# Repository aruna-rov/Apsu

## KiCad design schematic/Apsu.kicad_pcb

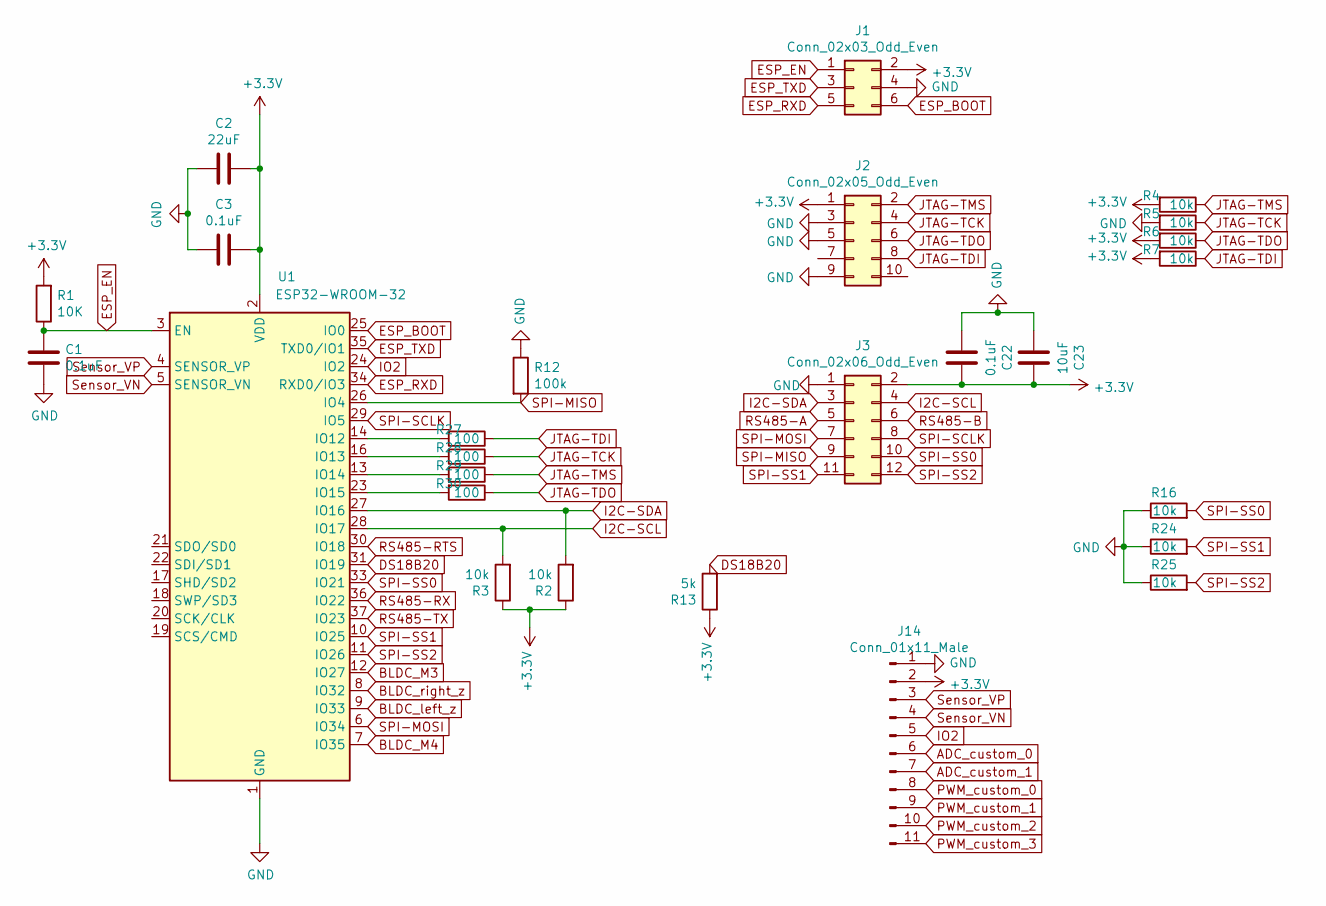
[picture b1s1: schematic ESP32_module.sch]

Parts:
C1, C3, C22: 0.1uF; C_0805_2012Metric_Pad1.15x1.40mm_HandSolder; MPN C0805C104J5RACTU
C2: 22uF; C_0805_2012Metric_Pad1.15x1.40mm_HandSolder; MPN C0805C226K9PACTU
C23: 10uF; C_0805_2012Metric_Pad1.15x1.40mm_HandSolder; MPN C0805C106K8PACTU
J1: Conn_02x03_Odd_Even; PinHeader_2x03_P1.27mm_Vertical_IDC; MPN GRPB032VWVN-RC
J2: Conn_02x05_Odd_Even; 10pin1.27mmIDC; MPN 3220-10-0100-00
J3: Conn_02x06_Odd_Even; IDC-Header_2x06_P2.54mm_Vertical; MPN BHR-12-VUA
J14: Conn_01x11_Male; PinHeader_1x11_P2.54mm_Vertical
R1: 10K; R_0805_2012Metric_Pad1.15x1.40mm_HandSolder; MPN ERA-6AEB103V
R2, R3, R4, R5, R6, R7, R16, R24, R25: 10k; R_0805_2012Metric_Pad1.15x1.40mm_HandSolder; MPN ERA-6AEB103V
R12: 100k; R_0805_2012Metric_Pad1.15x1.40mm_HandSolder; MPN ERA-6AEB104V
R13: 5k; R_0805_2012Metric_Pad1.15x1.40mm_HandSolder; MPN ERA6AEB4991V
R27, R28, R29, R30: 100; R_0805_2012Metric_Pad1.15x1.40mm_HandSolder; MPN ERA6AEB101V
U1: ESP32-WROOM-32; MPN ESP32-WROOM-32D

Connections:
+3V3: C2.2, C3.2, C22.2, C23.2, J1.2, J2.1, J3.2, J14.2, R1.2, R2.1, R3.1, R4.2, R6.2, R7.2, R13.1, U1.2 (VDD); also elsewhere on the board
ADC_custom_0: J14.6; also elsewhere on the board
ADC_custom_1: J14.7; also elsewhere on the board
BLDC_M3: U1.12 (IO27); also elsewhere on the board
BLDC_M4: U1.7 (IO35); also elsewhere on the board
BLDC_left_z: U1.9 (IO33); also elsewhere on the board
BLDC_right_z: U1.8 (IO32); also elsewhere on the board
DS18B20: R13.2, U1.31 (IO19); also elsewhere on the board
ESP_BOOT: J1.6, U1.25 (IO0)
ESP_EN: C1.1, J1.1, R1.1, U1.3 (EN)
ESP_RXD: J1.5, U1.34 (RXD0/IO3)
ESP_TXD: J1.3, U1.35 (TXD0/IO1)
GND: C1.2, C2.1, C3.1, C22.1, C23.1, J1.4, J2.3, J2.5, J2.9, J3.1, J14.1, R5.2, R12.1, R16.1, R24.1, R25.1, U1.1 (GND), U1.15 (GND), U1.38 (GND), U1.39 (GND); also elsewhere on the board
I2C-SCL: J3.4, R3.2, U1.28 (IO17); also elsewhere on the board
I2C-SDA: J3.3, R2.2, U1.27 (IO16); also elsewhere on the board
IO2: J14.5, U1.24 (IO2)
JTAG-TCK: J2.4, R5.1, R28.1
JTAG-TDI: J2.8, R7.1, R27.1
JTAG-TDO: J2.6, R6.1, R30.1
JTAG-TMS: J2.2, R4.1, R29.1
unnamed: R27.2, U1.14 (IO12)
unnamed: R28.2, U1.16 (IO13)
unnamed: R29.2, U1.13 (IO14)
unnamed: R30.2, U1.23 (IO15)
PWM_custom_0: J14.8; also elsewhere on the board
PWM_custom_1: J14.9; also elsewhere on the board
PWM_custom_2: J14.10; also elsewhere on the board
PWM_custom_3: J14.11; also elsewhere on the board
RS485-A: J3.5; also elsewhere on the board
RS485-B: J3.6; also elsewhere on the board
RS485-RTS: U1.30 (IO18); also elsewhere on the board
RS485-RX: U1.36 (IO22); also elsewhere on the board
RS485-TX: U1.37 (IO23); also elsewhere on the board
SPI-MISO: J3.9, R12.2, U1.26 (IO4); also elsewhere on the board
SPI-MOSI: J3.7, U1.6 (IO34)
SPI-SCLK: J3.8, U1.29 (IO5); also elsewhere on the board
SPI-SS0: J3.10, R16.2, U1.33 (IO21); also elsewhere on the board
SPI-SS1: J3.11, R24.2, U1.10 (IO25); also elsewhere on the board
SPI-SS2: J3.12, R25.2, U1.11 (IO26); also elsewhere on the board
Sensor_VN: J14.4, U1.5 (SENSOR_VN)
Sensor_VP: J14.3, U1.4 (SENSOR_VP)

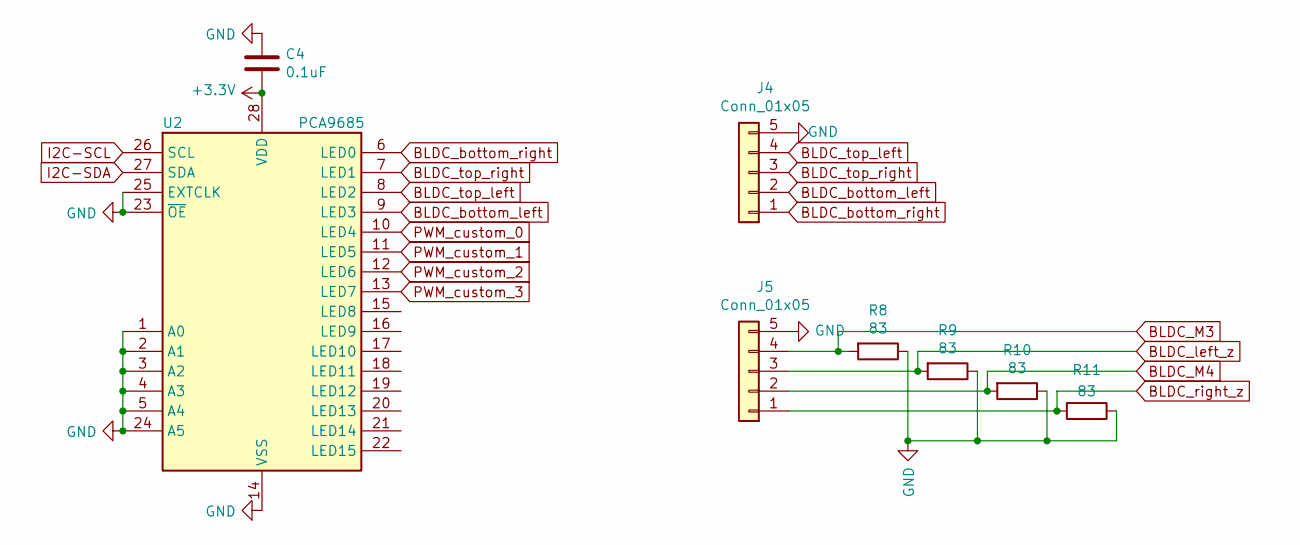
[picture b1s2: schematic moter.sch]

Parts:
C4: 0.1uF; C_0805_2012Metric_Pad1.15x1.40mm_HandSolder; MPN C0805C104J5RACTU
J4, J5: Conn_01x05; JST_XH_B5B-XH-A_1x05_P2.50mm_Vertical; MPN B5B-XH-A(LF)(SN)
R8, R9, R10, R11: 83; R_0805_2012Metric_Pad1.15x1.40mm_HandSolder; MPN ERA-6AEB820V
U2: PCA9685; NXP_Semiconductors-SOT788-1-02_2016-0-MFG; MPN PCA9685BS,118

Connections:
+3V3: C4.2, U2.28 (VDD); also elsewhere on the board
BLDC_M3: J5.4, R8.2; also elsewhere on the board
BLDC_M4: J5.2, R10.2; also elsewhere on the board
BLDC_bottom_left: J4.2, U2.9 (LED3)
BLDC_bottom_right: J4.1, U2.6 (LED0)
BLDC_left_z: J5.3, R9.2; also elsewhere on the board
BLDC_right_z: J5.1, R11.2; also elsewhere on the board
BLDC_top_left: J4.4, U2.8 (LED2)
BLDC_top_right: J4.3, U2.7 (LED1)
GND: C4.1, J4.5, J5.5, R8.1, R9.1, R10.1, R11.1, U2.1 (A0), U2.2 (A1), U2.3 (A2), U2.4 (A3), U2.5 (A4), U2.14 (VSS), U2.23 (~OE), U2.24 (A5), U2.25 (EXTCLK); also elsewhere on the board
I2C-SCL: U2.26 (SCL); also elsewhere on the board
I2C-SDA: U2.27 (SDA); also elsewhere on the board
PWM_custom_0: U2.10 (LED4); also elsewhere on the board
PWM_custom_1: U2.11 (LED5); also elsewhere on the board
PWM_custom_2: U2.12 (LED6); also elsewhere on the board
PWM_custom_3: U2.13 (LED7); also elsewhere on the board

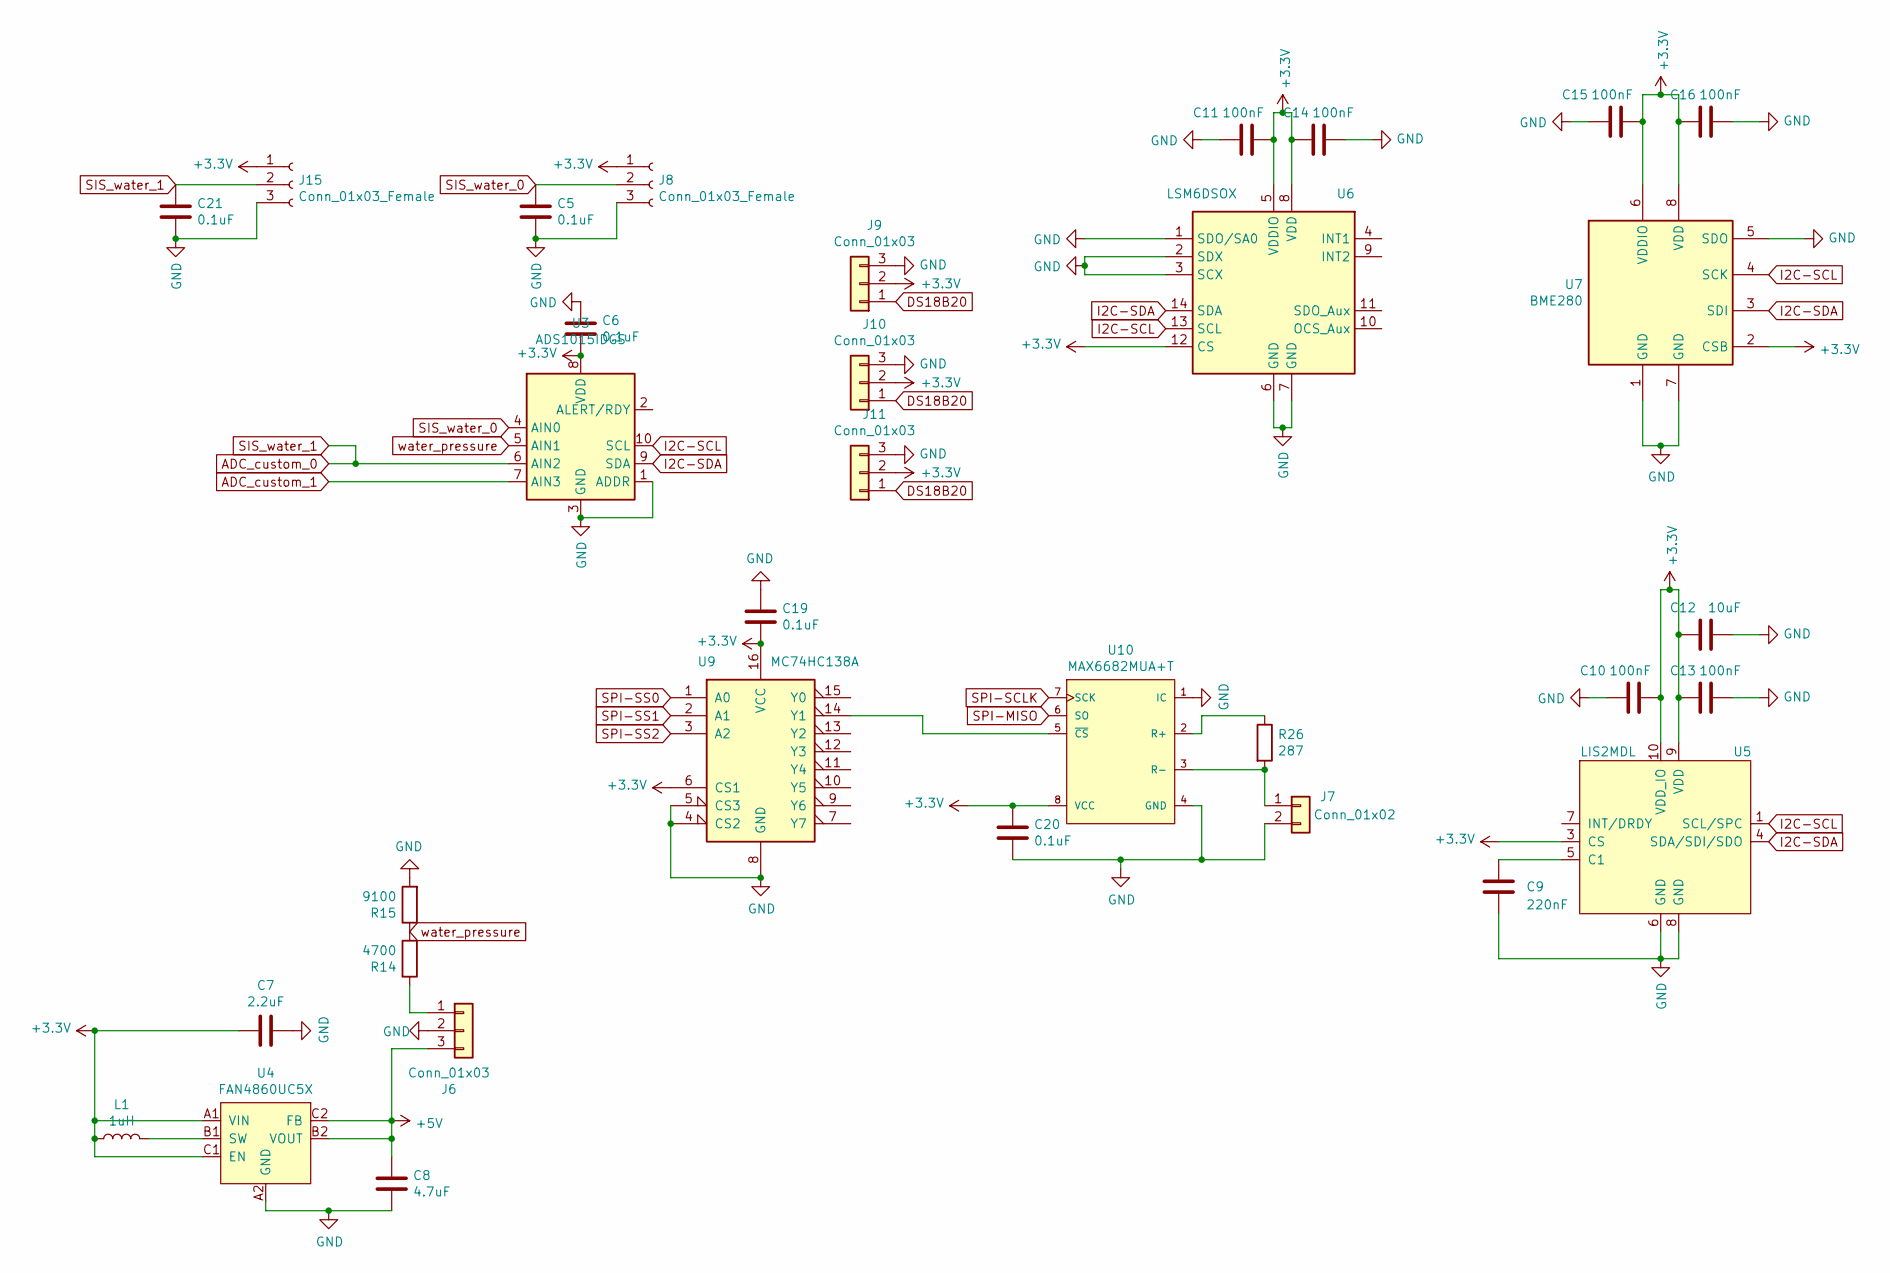
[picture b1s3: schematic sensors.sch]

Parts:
C5, C6, C19, C20, C21: 0.1uF; C_0805_2012Metric_Pad1.15x1.40mm_HandSolder; MPN C0805C104J5RACTU
C7: 2.2uF; C_0805_2012Metric_Pad1.15x1.40mm_HandSolder; MPN C0805C225K4RACTU
C8: 4.7uF; C_0805_2012Metric_Pad1.15x1.40mm_HandSolder; MPN C0805C475K3PACTU
C9: 220nF; C_0805_2012Metric_Pad1.15x1.40mm_HandSolder; MPN C0805C224K5RACTU
C10, C11, C13, C14, C15, C16: 100nF; C_0805_2012Metric_Pad1.15x1.40mm_HandSolder; MPN C0805C104J5RACTU
C12: 10uF; C_0805_2012Metric_Pad1.15x1.40mm_HandSolder; MPN C0805C106K8PACTU
J6, J9, J10, J11: Conn_01x03; JST_XH_B3B-XH-A_1x03_P2.50mm_Vertical; MPN B3B-XH-A(LF)(SN)
J7: Conn_01x02; JST_XH_B2B-XH-A_1x02_P2.50mm_Vertical; MPN B2B-XH-A(LF)(SN)
J8, J15: Conn_01x03_Female; JST_XH_B3B-XH-A_1x03_P2.50mm_Vertical; MPN B3B-XH-A(LF)(SN)
L1: 1uH; L_0805_2012Metric_Pad1.15x1.40mm_HandSolder; MPN LQM21NN1R0K10D
R14: 4700; R_0805_2012Metric_Pad1.15x1.40mm_HandSolder; MPN ERA-6AEB472V
R15: 9100; R_0805_2012Metric_Pad1.15x1.40mm_HandSolder; MPN ERA6AEB912V
R26: 287; R_0805_2012Metric_Pad1.15x1.40mm_HandSolder; MPN ERA-6AEB301V
U3: ADS1015IDGS; TSSOP-10_3x3mm_P0.5mm; MPN ADS1015IDGS
U4: FAN4860UC5X; WLCSP-6_1.4x1.0mm_P0.4mm; MPN FAN4860UC5X
U5: LIS2MDL; LGA-12_2x2mm_P0.5mm; MPN LIS2MDLTR
U6: LSM6DSOX; LGA-14_3x2.5mm_P0.5mm_LayoutBorder3x4y; MPN LSM6DSOXTR
U7: BME280; Bosch_LGA-8_2.5x2.5mm_P0.65mm_ClockwisePinNumbering; MPN BME280
U9: MC74HC138A; TSSOP-16_4.4x5mm_P0.65mm; MPN MC74HC138ADTR2G
U10: MAX6682MUA+T; Maxim-MAX6682MUA+T-Level_A; MPN MAX6682MUA+T

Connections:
+3V3: C6.2, C7.2, C10.2, C11.2, C12.1, C13.1, C14.1, C15.2, C16.1, C19.2, C20.1, J8.1, J9.2, J10.2, J11.2, J15.1, L1.1, U3.8 (VDD), U4.A1 (VIN), U4.C1 (EN), U5.3 (CS), U5.9 (VDD), U5.10 (VDD_IO), U6.5 (VDDIO), U6.8 (VDD), U6.12 (CS), U7.2 (CSB), U7.6 (VDDIO), U7.8 (VDD), U9.6 (CS1), U9.16 (VCC), U10.8 (VCC); also elsewhere on the board
+5V: C8.1, J6.3, U4.B2 (VOUT), U4.C2 (FB)
ADC_custom_0: C21.1, J15.2, U3.6 (AIN2); also elsewhere on the board
ADC_custom_1: U3.7 (AIN3); also elsewhere on the board
DS18B20: J9.1, J10.1, J11.1; also elsewhere on the board
GND: C5.2, C6.1, C7.1, C8.2, C9.2, C10.1, C11.1, C12.2, C13.2, C14.2, C15.1, C16.2, C19.1, C20.2, C21.2, J6.2, J7.2, J8.3, J9.3, J10.3, J11.3, J15.3, R15.2, U3.1 (ADDR), U3.3 (GND), U4.A2 (GND), U5.6 (GND), U5.8 (GND), U6.1 (SDO/SA0), U6.2 (SDX), U6.3 (SCX), U6.6 (GND), U6.7 (GND), U7.1 (GND), U7.5 (SDO), U7.7 (GND), U9.4 (CS2), U9.5 (CS3), U9.8 (GND), U10.1 (IC), U10.4 (GND); also elsewhere on the board
I2C-SCL: U3.10 (SCL), U5.1 (SCL/SPC), U6.13 (SCL), U7.4 (SCK); also elsewhere on the board
I2C-SDA: U3.9 (SDA), U5.4 (SDA/SDI/SDO), U6.14 (SDA), U7.3 (SDI); also elsewhere on the board
unnamed: C9.1, U5.5 (C1)
unnamed: J6.1, R14.1
unnamed: J7.1, R26.2, U10.3 (R-)
unnamed: L1.2, U4.B1 (SW)
unnamed: R26.1, U10.2 (R+)
unnamed: U9.14 (Y1), U10.5 (~CS~)
SIS_water_0: C5.1, J8.2, U3.4 (AIN0)
SPI-MISO: U10.6 (SO); also elsewhere on the board
SPI-SCLK: U10.7 (SCK); also elsewhere on the board
SPI-SS0: U9.1 (A0); also elsewhere on the board
SPI-SS1: U9.2 (A1); also elsewhere on the board
SPI-SS2: U9.3 (A2); also elsewhere on the board
water_pressure: R14.2, R15.1, U3.5 (AIN1)

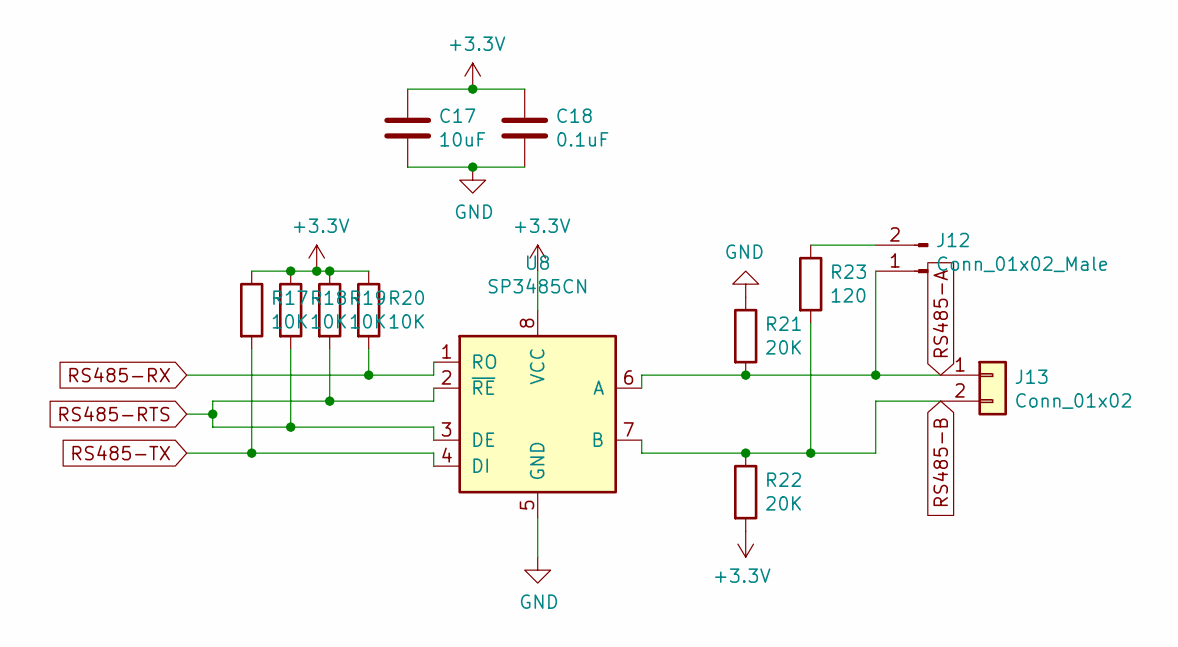
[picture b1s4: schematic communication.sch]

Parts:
C17: 10uF; C_0805_2012Metric_Pad1.15x1.40mm_HandSolder; MPN C0805C106K8PACTU
C18: 0.1uF; C_0805_2012Metric_Pad1.15x1.40mm_HandSolder; MPN C0805C104J5RACTU
J12: Conn_01x02_Male; PinHeader_1x02_P2.54mm_Vertical
J13: Conn_01x02; JST_XH_B2B-XH-A_1x02_P2.50mm_Vertical; MPN B2B-XH-A(LF)(SN)
R17, R18, R19, R20: 10K; R_0805_2012Metric_Pad1.15x1.40mm_HandSolder; MPN ERA-6AEB103V
R21, R22: 20K; R_0805_2012Metric_Pad1.15x1.40mm_HandSolder; MPN ERA6AEB203V
R23: 120; R_0805_2012Metric_Pad1.15x1.40mm_HandSolder; MPN ERJ-6ENF1200V
U8: SP3485CN; SOIC-8_3.9x4.9mm_P1.27mm; MPN MAX485CSA+

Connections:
+3V3: C17.1, C18.1, R17.1, R18.1, R19.1, R20.1, R22.2, U8.8 (VCC); also elsewhere on the board
GND: C17.2, C18.2, R21.1, U8.5 (GND); also elsewhere on the board
unnamed: J12.2, R23.1
RS485-A: J12.1, J13.1, R21.2, U8.6 (A); also elsewhere on the board
RS485-B: J13.2, R22.1, R23.2, U8.7 (B); also elsewhere on the board
RS485-RTS: R18.2, R19.2, U8.2 (~RE~), U8.3 (DE); also elsewhere on the board
RS485-RX: R20.2, U8.1 (RO); also elsewhere on the board
RS485-TX: R17.2, U8.4 (DI); also elsewhere on the board

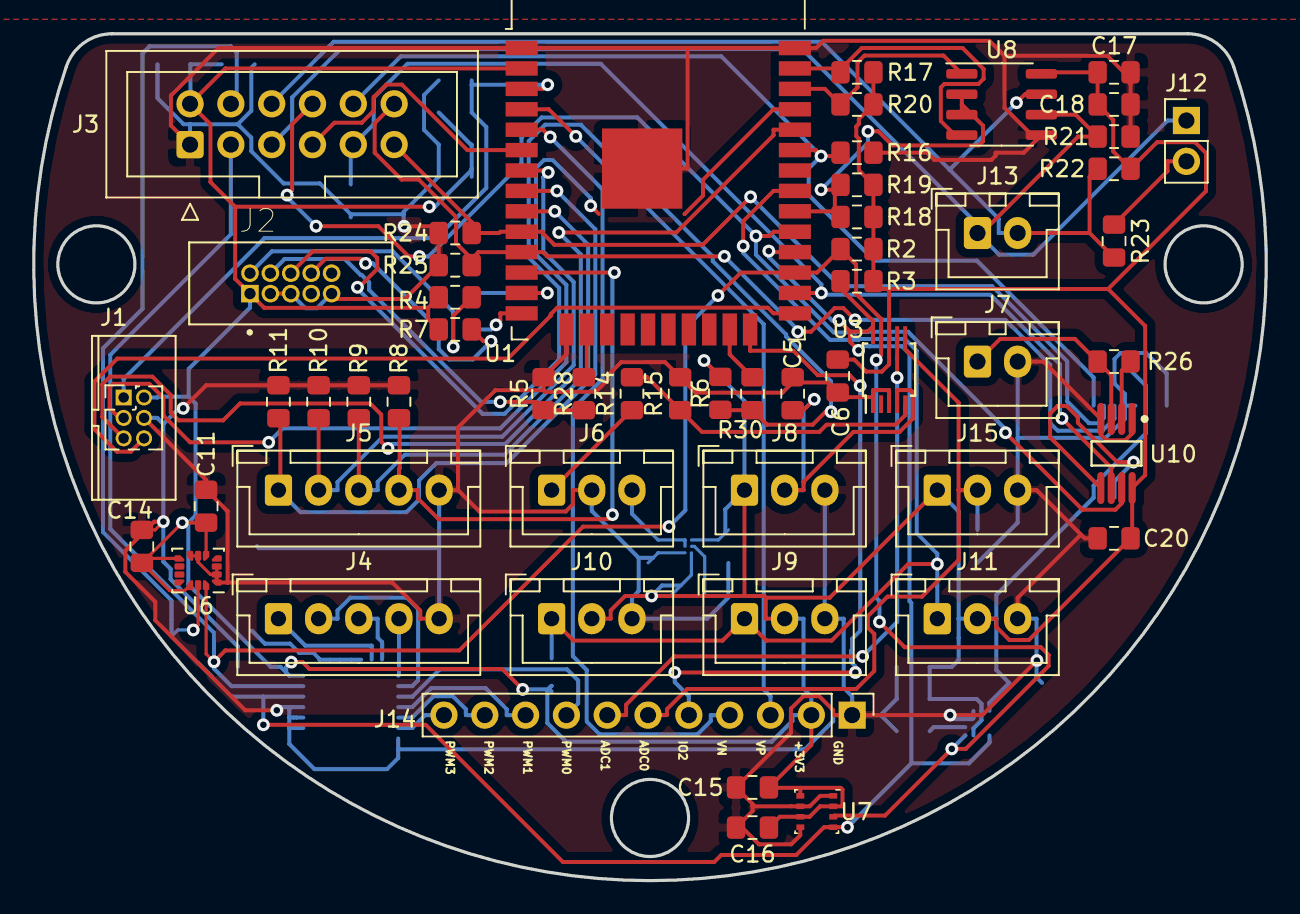
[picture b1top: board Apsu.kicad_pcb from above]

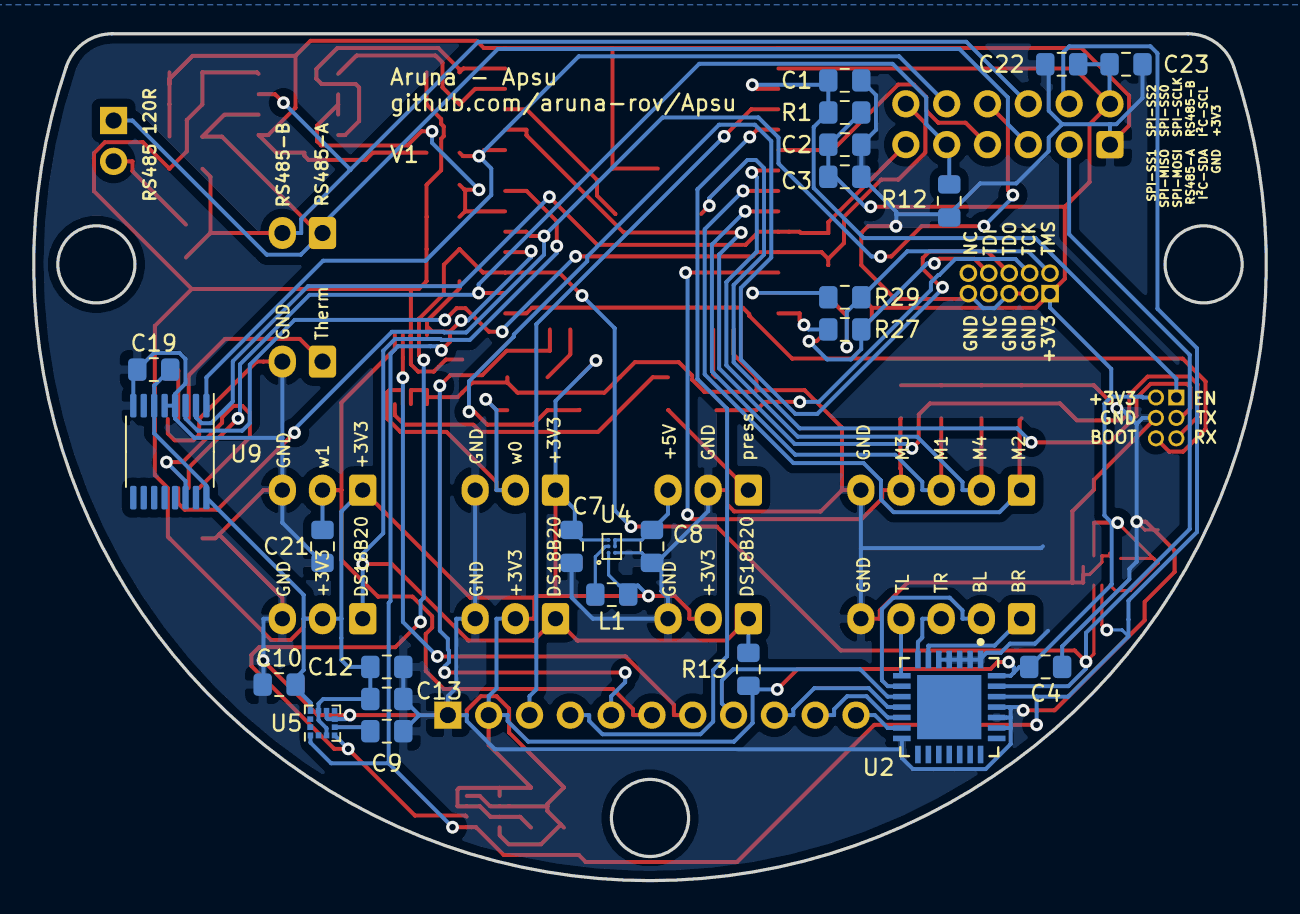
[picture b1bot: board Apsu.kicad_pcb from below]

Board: 2 copper layers, 76.7 x 52.7 mm, 79 parts (24 on the bottom side), 55 nets.

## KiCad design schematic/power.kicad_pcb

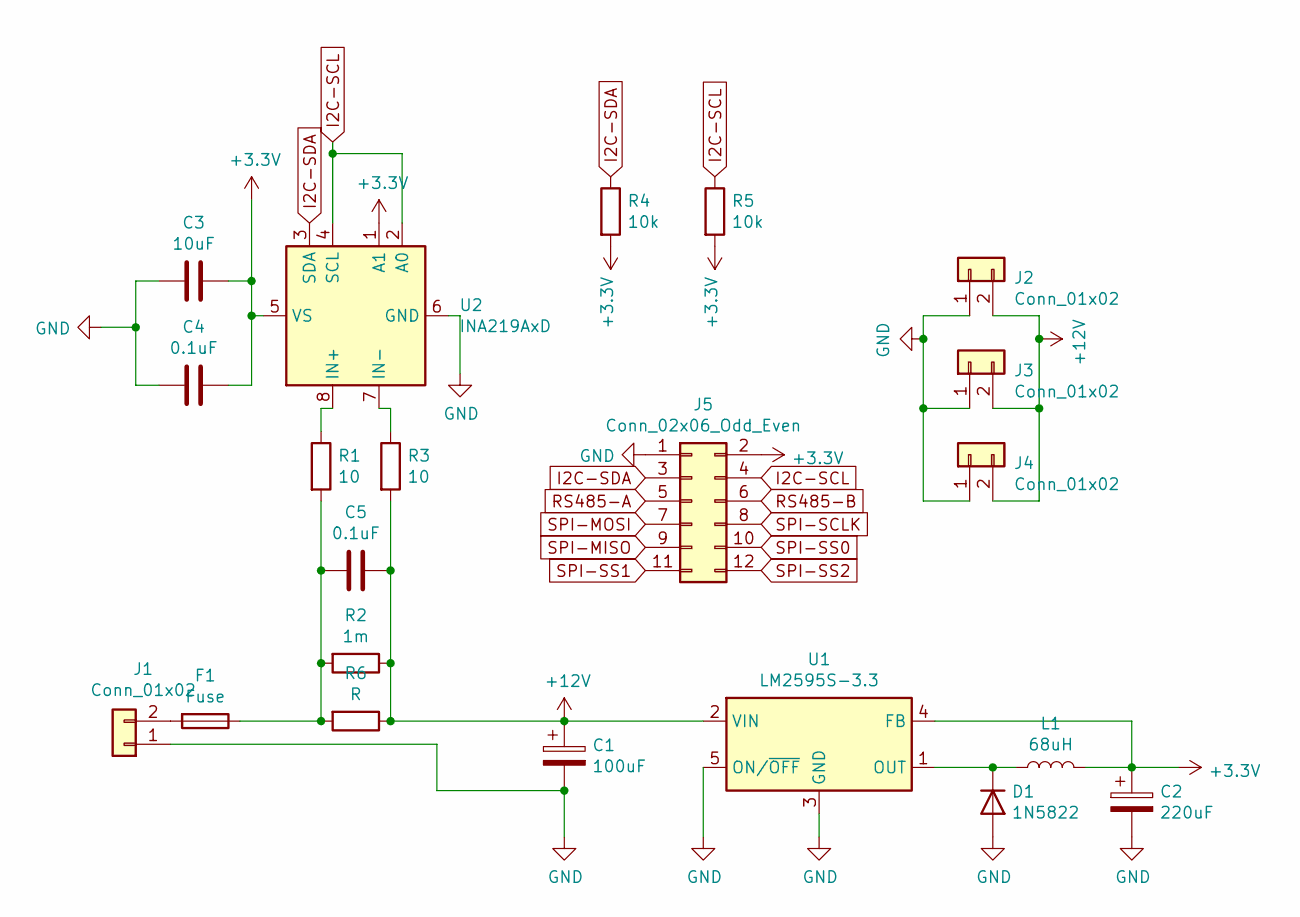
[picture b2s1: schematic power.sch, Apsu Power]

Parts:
C1: 100uF; CP_Radial_D10.0mm_P5.00mm; MPN EEUTP1V101
C2: 220uF; CP_Radial_D8.0mm_P3.50mm; MPN ESW227M035AG4AA
C3: 10uF; C_0805_2012Metric_Pad1.15x1.40mm_HandSolder; MPN C0805C106K8PACTU
C4, C5: 0.1uF; C_0805_2012Metric_Pad1.15x1.40mm_HandSolder; MPN C0805C104J5RACTU
D1: 1N5822; D_DO-201AD_P15.24mm_Horizontal; MPN 1N5822
F1: Fuse; Fuseholder_Cylinder-5x20mm_Schurter_0031_8201_Horizontal_Op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
J1: Conn_01x02; AMASS_XT60-M_1x02_P7.20mm_Vertical; MPN PRT-10474
J2, J3, J4: Conn_01x02; AMASS_XT60-F_1x02_P7.20mm_Vertical; MPN PRT-10474
J5: Conn_02x06_Odd_Even; IDC-Header_2x06_P2.54mm_Vertical; MPN BHR-12-VUA
L1: 68uH; L_Radial_L16.1mm_W16.1mm_Px7.62mm_Py12.70mm_Pulse_LP-44; MPN PE-53830NL
R1, R3: 10; R_0805_2012Metric_Pad1.15x1.40mm_HandSolder; MPN ERJ-P06J100V
R2: 1m; R_2512_6332Metric_Pad1.52x3.35mm_HandSolder; MPN CSNL2512FT1L00
R4, R5: 10k; R_0805_2012Metric_Pad1.15x1.40mm_HandSolder; MPN ERA-6AEB103V
R6: R; R_Axial_DIN0207_L6.3mm_D2.5mm_P10.16mm_Horizontal
U1: LM2595S-3.3; TO-263-5_TabPin3; MPN LM2595S-3.3/NOPB
U2: INA219AxD; SOIC-8_3.9x4.9mm_P1.27mm; MPN INA219AIDR

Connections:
+3V3: C2.1, C3.1, C4.1, J5.2, L1.2, R4.2, R5.2, U1.4 (FB), U2.1 (A1), U2.5 (VS)
+12V: C1.1, C5.1, J2.2, J3.2, J4.2, R2.1, R3.2, R6.1, U1.2 (VIN)
GND: C1.2, C2.2, C3.2, C4.2, D1.2 (A), J1.1, J2.1, J3.1, J4.1, J5.1, U1.3 (GND), U1.5 (ON/~OFF), U2.6 (GND)
I2C-SCL: J5.4, R5.1, U2.2 (A0), U2.4 (SCL)
I2C-SDA: J5.3, R4.1, U2.3 (SDA)
unnamed: C5.2, F1.1, R1.2, R2.2, R6.2
unnamed: D1.1 (K), L1.1, U1.1 (OUT)
unnamed: F1.2, J1.2
unnamed: R1.1, U2.8 (IN+)
unnamed: R3.1, U2.7 (IN-)
RS485-A: J5.5
RS485-B: J5.6
SPI-MISO: J5.9
SPI-MOSI: J5.7
SPI-SCLK: J5.8
SPI-SS0: J5.10
SPI-SS1: J5.11
SPI-SS2: J5.12

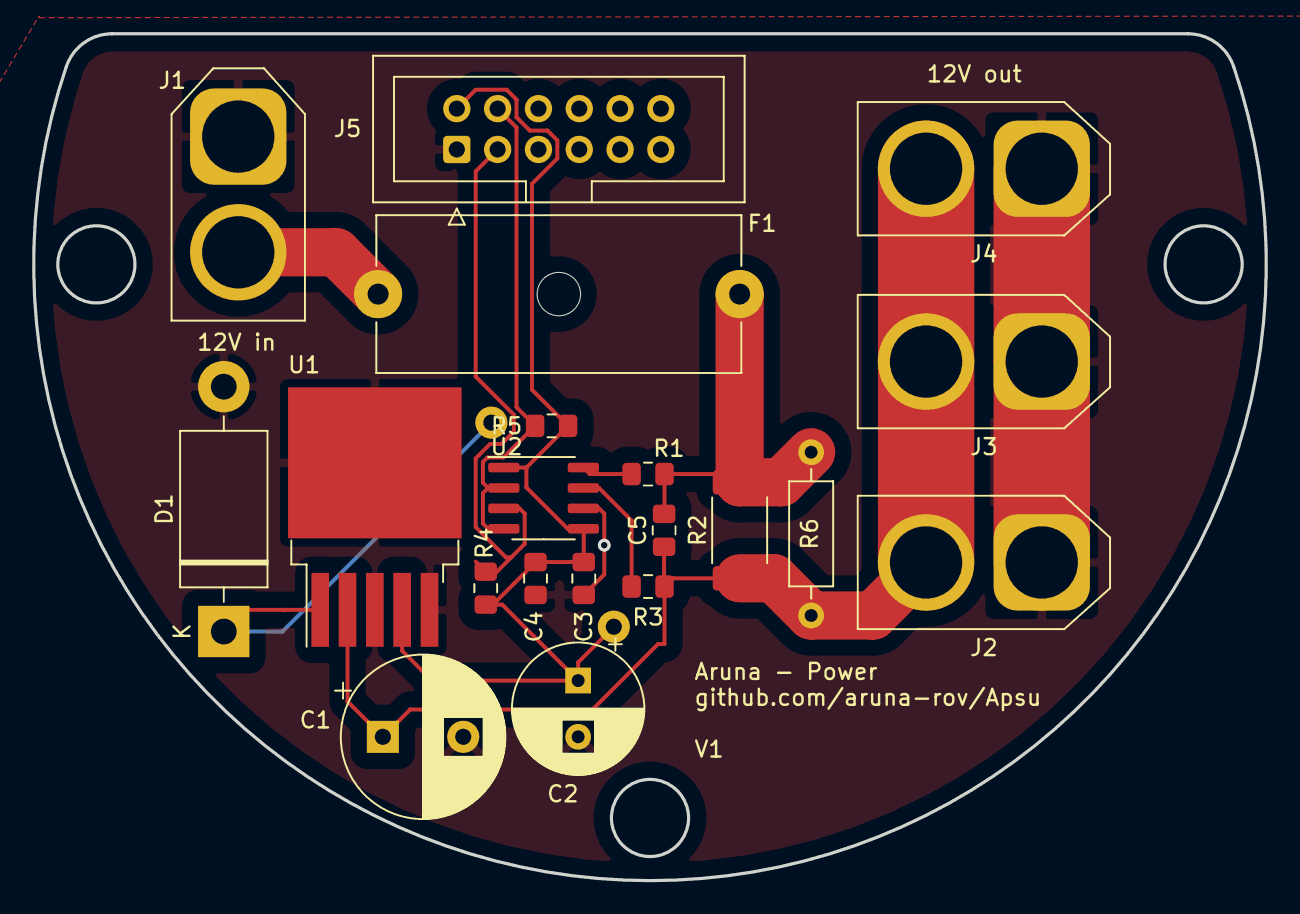
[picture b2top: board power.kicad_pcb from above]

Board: 2 copper layers, 76.7 x 52.7 mm, 21 parts (1 on the bottom side), 10 nets.

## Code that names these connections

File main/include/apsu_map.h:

//
// Created by noeel on 21-08-20.
//

#ifndef APSU_MAP_H
#define APSU_MAP_H

enum class I2C_address: uint8_t {
    ADS1015     = 0b1001000,
    LSM6DSOX    = 0b1101010,
    BME280      = 0b1110110,
    IIS2MDL     = 0b0011110,
    PCA9685     = 0b1000000,
    INA219      = 0b1000111,
};

enum class IO {
    ESP_TXD     = 1,
    ESP_RXD     = 3,
    SPI_MISO    = 4,
    SPI_SCLK    = 5,
    I2C_SDA     = 16,
    I2C_SCL     = 17,
    RS485_RTS   = 18,
    DS18B20     = 19,
    SPI_SS0     = 21,
    RS485_RX    = 22,
    RS485_TX    = 23,
    SPI_SS1     = 25,
    SPI_SS2     = 26,
    BLDC_M3     = 27,
    BLDC_RIGHT_Z= 32,
    BLDC_LEFT_Z = 33,
    SPI_MOSI    = 34,
    BLDC_M4     = 35,
};

enum class PCA9685_LED {
    BLDC_bottom_right = 15,
    BLDC_top_right = 13,
    BLDC_top_left = 12,
    BLDC_bottom_left = 14,
};
#endif //APSU_MAP_H

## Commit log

2019-07-04 init
2019-07-04 added Aruna library
2019-07-08 New Aruna version
2019-07-17 updated aruna lib
2019-08-07 updated Aruna, implemented comm and control
2019-11-06 added bldc motors
2020-01-04 Put bldc motors in off modes
2020-03-30 removed unused drivers
2020-03-30 cleared JTAG pins
2020-03-30 Dshot Z drivers
2020-04-20 SIS water reporter and lowered baudrate
2020-04-26 pwm startup fix
2020-04-26 removed MPU driver
2020-05-14 Apsu schematic init
2020-05-19 prototype board state
2020-05-19 more connectors
2020-05-22 dingentjes
2020-05-22 SIS water to I2C and added SPI
2020-05-22 SimonK BLDC to I2C -> PWM
2020-05-22 added DS18B20 conn
2020-05-23 voltage divider
2020-05-31 moved everything in seperated schematics
2020-05-31 prototype footprint and placement test
2020-06-08 added LSM6DSOX and LIS2MDL for IMU
2020-06-10 added BME280
2020-06-10 added pcb design
2020-06-10 new pcb design
2020-06-17 SP385 instead of MAX
2020-06-17 Cleared IO2
2020-06-17 BLHeli pull-down
2020-06-17 SPI SS multiplex concept
2020-06-17 power on seperate board
2020-06-20 added 5v boost converter
2020-06-24 boost converter on Apsu board and PCB design
2020-06-24 added 14pin header
2020-06-24 wire documentation
2020-06-25 added MAX6682 for termistor
2020-06-26 new components on pcb
2020-07-03 datasheets
2020-07-03 JTAG anti-ring resistors
2020-07-04 adjusted 1.27mm IDC and PCA9685 to correct footprint
2020-07-06 wireing
2020-07-07 on-pcb documentation
2020-07-08 added extra resistor, removed unnessesary components and added traces to power board
2020-07-10 power documentation
2020-07-11 prototype PCB
2020-07-13 correct power D1, C1, C2 and L1 footprint. accurate L1, D1 and C2 values
2020-07-13 lm2596 and D1 datasheet
2020-07-15 added version
2020-07-18 added MPN
2020-08-03 added MPN for connectors
2020-08-03 resistor and capacitor datasheet
2020-08-07 ignore more
2020-08-17 openocd cfg
2020-08-21 Apsu map
2020-08-28 GNU GPLv3 license
2020-09-16 iis2mdc datasheet
2020-09-16 ADS101x SIS water
2020-09-25 PCA9685 PWM
2021-04-12 updated to newest Aruna version
